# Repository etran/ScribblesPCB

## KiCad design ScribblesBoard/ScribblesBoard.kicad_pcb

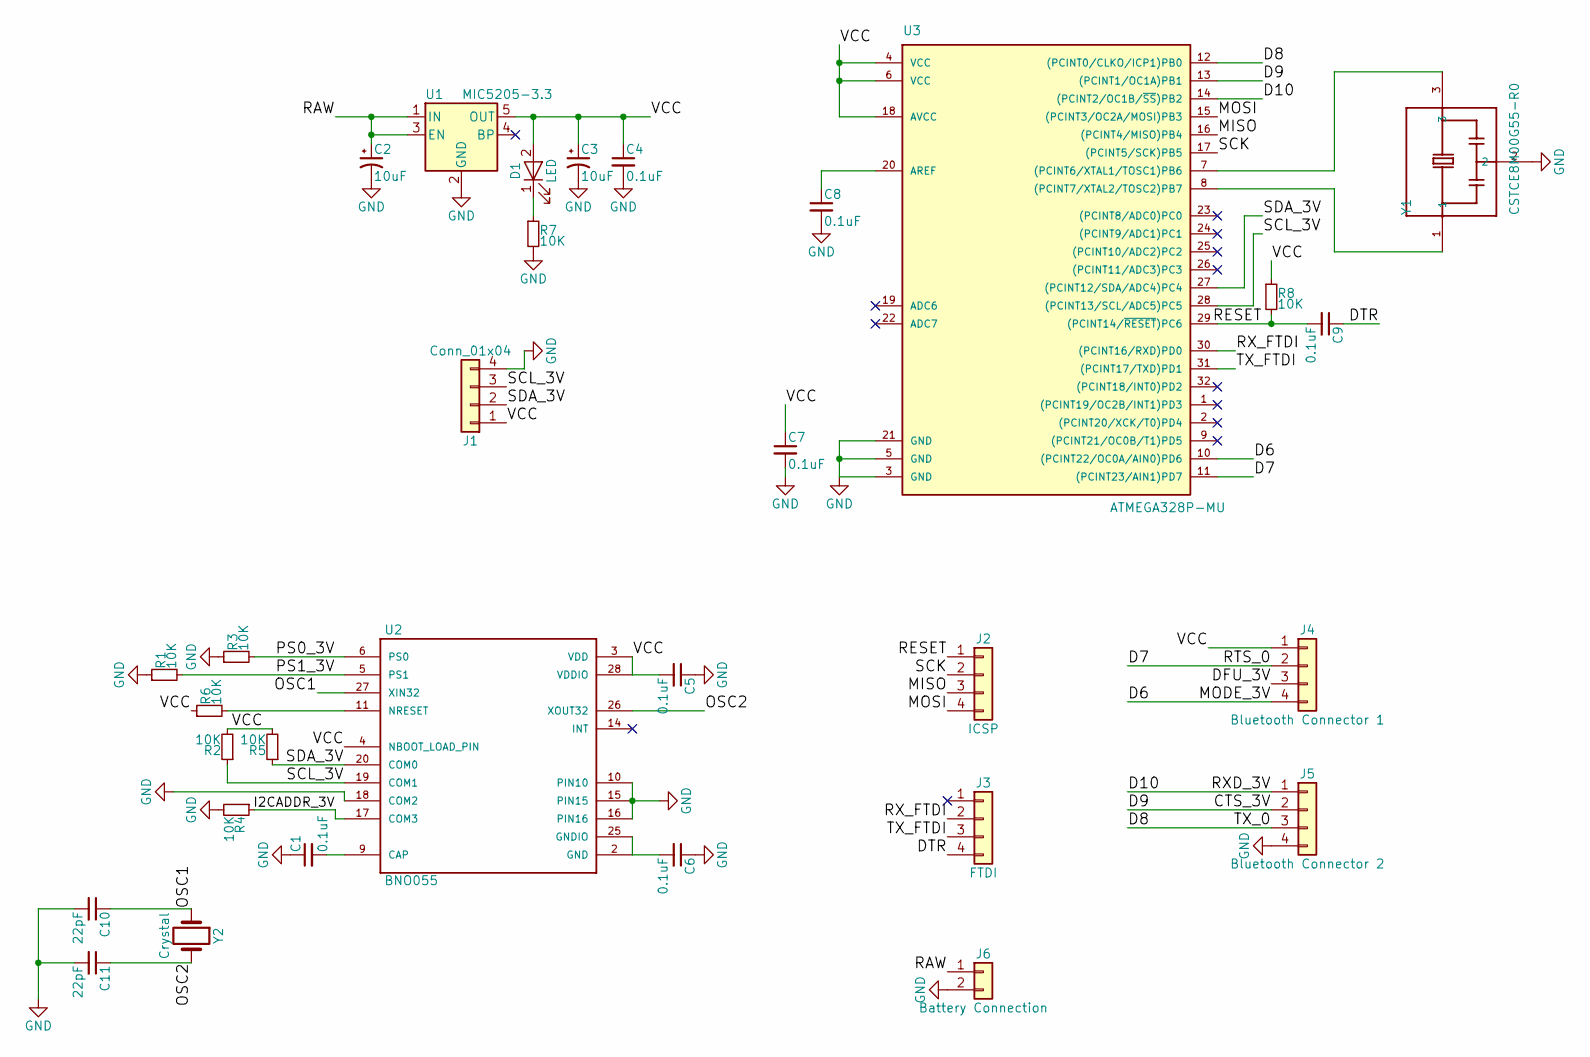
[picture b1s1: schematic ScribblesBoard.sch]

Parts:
C1, C4, C5, C6, C7, C8, C9: 0.1uF; C_0402
C2, C3: 10uF; C_0603
C10, C11: 22pF; C_0402
D1: LED; LED_0603
J1: Conn_01x04; Pin_Header_Straight_1x04_Pitch2.54mm
J2: ICSP; Pin_Header_Straight_1x04_Pitch2.54mm
J3: FTDI; Pin_Header_Straight_1x04_Pitch2.54mm
J4: Bluetooth Connector 1; Pin_Header_Straight_1x04_Pitch2.54mm
J5: Bluetooth Connector 2; Pin_Header_Straight_1x04_Pitch2.54mm
J6: Battery Connection; Pin_Header_Straight_1x02_Pitch2.54mm
R1, R2, R3, R4, R5, R6, R7, R8: 10K; R_0402
U1: MIC5205-3.3; SOT-23-5
U2: BNO055; LGA28R50P4X10_380X520X100
U3: ATMEGA328P-MU; QFN50P500X500X100-33N
Y1: CSTCE8M00G55-R0; OSC_CSTCE8M00G55-R0
Y2: Crystal; ECS-.327-12.5-34B-TR

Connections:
/CTS_3V: J5.2, U3.13 ((PCINT1/OC1A)PB1)
/D6: J4.4, U3.10 ((PCINT22/OC0A/AIN0)PD6)
/D7: J4.2, U3.11 ((PCINT23/AIN1)PD7)
/D8: J5.3, U3.12 ((PCINT0/CLKO/ICP1)PB0)
/D10: J5.1, U3.14 ((PCINT2/OC1B/~SS~)PB2)
/DFU_3V: J4.3
/DTR: C9.1, J3.4
/I2CADDR_3V: R4.1, U2.17 (COM3)
/MISO: J2.3, U3.16 ((PCINT4/MISO)PB4)
/MOSI: J2.4, U3.15 ((PCINT3/OC2A/MOSI)PB3)
/OSC1: C10.1, U2.27 (XIN32), Y2.1
/OSC2: C11.1, U2.26 (XOUT32), Y2.2
/PS0_3V: R3.2, U2.6 (PS0)
/PS1_3V: R1.2, U2.5 (PS1)
/RAW: C2.1, J6.1, U1.1 (IN), U1.3 (EN)
/RESET: C9.2, J2.1, R8.2, U3.29 ((PCINT14/~RESET~)PC6)
/RX_FTDI: J3.2, U3.30 ((PCINT16/RXD)PD0)
/SCK: J2.2, U3.17 ((PCINT5/SCK)PB5)
/SCL_3V: J1.3, R2.1, U2.19 (COM1), U3.28 ((PCINT13/SCL/ADC5)PC5)
/SDA_3V: J1.2, R5.1, U2.20 (COM0), U3.27 ((PCINT12/SDA/ADC4)PC4)
/TX_FTDI: J3.3, U3.31 ((PCINT17/TXD)PD1)
/VCC: C3.1, C4.1, C5.2, C7.1, D1.2 (A), J1.1, J4.1, R2.2, R5.2, R6.1, R8.1, U1.5 (OUT), U2.3 (VDD), U2.4 (NBOOT_LOAD_PIN), U2.28 (VDDIO), U3.4 (VCC), U3.6 (VCC), U3.18 (AVCC)
GND: C1.1, C2.2, C3.2, C4.2, C5.1, C6.1, C7.2, C8.2, C10.2, C11.2, J1.4, J5.4, J6.2, R1.1, R3.1, R4.2, R7.2, U1.2 (GND), U2.10 (PIN10), U2.15 (PIN15), U2.16 (PIN16), U2.18 (COM2), U3.3 (GND), U3.5 (GND), U3.21 (GND), Y1.2
unnamed: C1.2, U2.9 (CAP)
unnamed: C6.2, U2.2 (GND), U2.25 (GNDIO)
unnamed: C8.1, U3.20 (AREF)
unnamed: D1.1 (K), R7.1
unnamed: R6.2, U2.11 (NRESET)
unnamed: U3.7 ((PCINT6/XTAL1/TOSC1)PB6), Y1.3
unnamed: U3.8 ((PCINT7/XTAL2/TOSC2)PB7), Y1.1

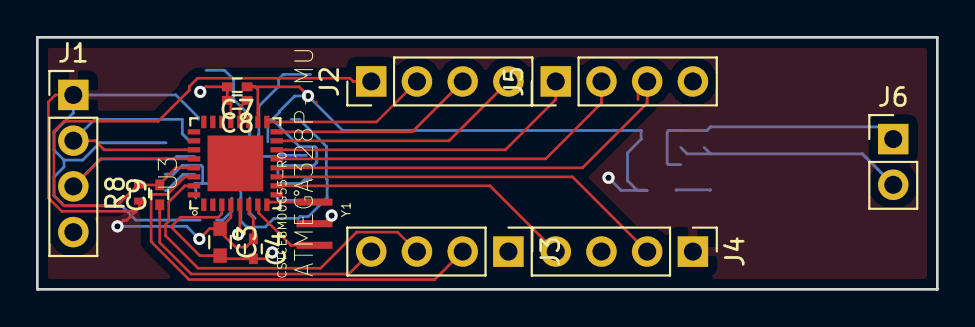
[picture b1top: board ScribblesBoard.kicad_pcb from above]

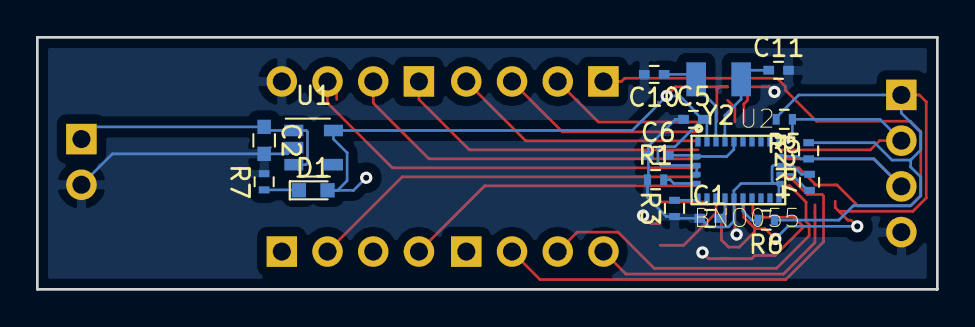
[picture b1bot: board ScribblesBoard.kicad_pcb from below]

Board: 2 copper layers, 50.0 x 14.0 mm, 31 parts (17 on the bottom side), 29 nets.

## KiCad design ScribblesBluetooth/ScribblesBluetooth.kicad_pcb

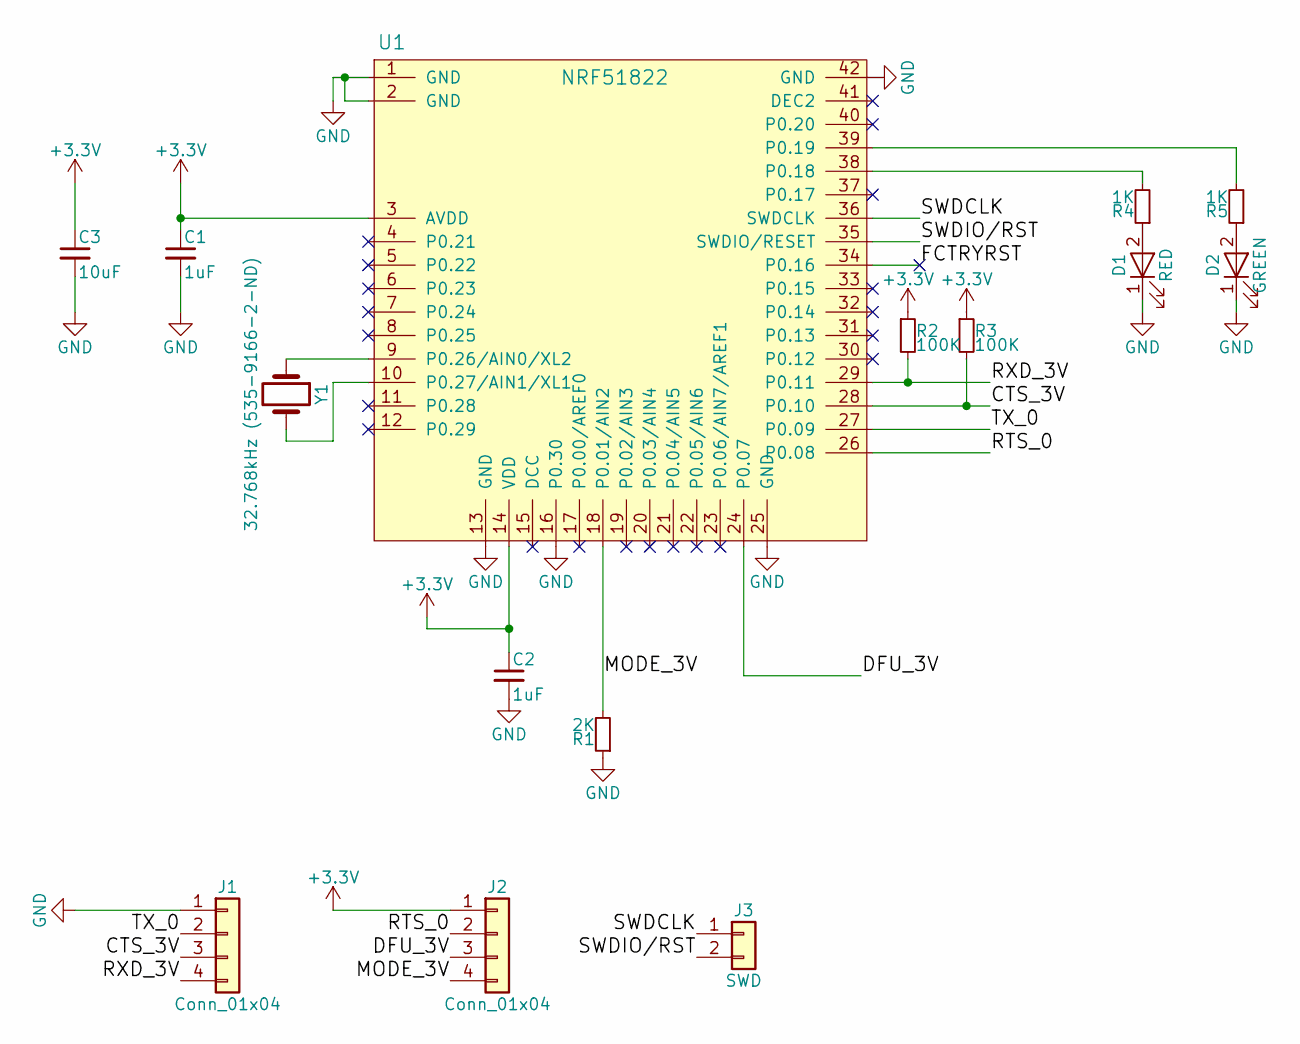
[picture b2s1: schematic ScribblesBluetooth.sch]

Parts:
C1, C2: 1uF; C_0402
C3: 10uF; C_0402
D1: RED; LED_0402
D2: GREEN; LED_0402
J1, J2: Conn_01x04; Pin_Header_Straight_1x04_Pitch2.54mm
J3: SWD; Pin_Header_Straight_1x02_Pitch2.54mm
R1: 2K; R_0402
R2, R3: 100K; R_0402
R4, R5: 1K; R_0402
U1: NRF51822
Y1: 32.768kHz (535-9166-2-ND); XTAL320X150X90N

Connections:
+3V3: C1.1, C2.1, C3.1, J2.1, R2.1, R3.1, U1.3 (AVDD), U1.14 (VDD)
/CTS_3V: J1.3, R3.2, U1.28 (P0.10)
/DFU_3V: J2.3, U1.24 (P0.07)
/FCTRYRST: U1.34 (P0.16)
/MODE_3V: J2.4, R1.2, U1.18 (P0.01/AIN2)
/RTS_0: J2.2, U1.26 (P0.08)
/RXD_3V: J1.4, R2.2, U1.29 (P0.11)
/SWDCLK: J3.1, U1.36 (SWDCLK)
/SWDIO/RST: J3.2, U1.35 (SWDIO/RESET)
/TX_0: J1.2, U1.27 (P0.09)
GND: C1.2, C2.2, C3.2, D1.1 (K), D2.1 (K), J1.1, R1.1, U1.1 (GND), U1.2 (GND), U1.13 (GND), U1.16 (P0.30), U1.25 (GND), U1.42 (GND)
unnamed: D1.2 (A), R4.1
unnamed: D2.2 (A), R5.1
unnamed: R4.2, U1.38 (P0.18)
unnamed: R5.2, U1.39 (P0.19)
unnamed: U1.9 (P0.26/AIN0/XL2), Y1.1
unnamed: U1.10 (P0.27/AIN1/XL1), Y1.2

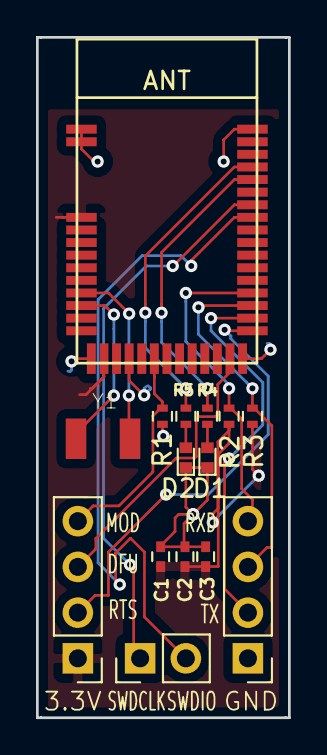
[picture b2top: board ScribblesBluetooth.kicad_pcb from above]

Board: 2 copper layers, 14.0 x 37.8 mm, 15 parts (0 on the bottom side), 16 nets.

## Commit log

2018-03-01 Initial commit of scribbles PCBs
2018-03-02 Finished bluetooth board
2018-03-03 Board without external oscillator
2018-03-04 Added oscillator to imu
